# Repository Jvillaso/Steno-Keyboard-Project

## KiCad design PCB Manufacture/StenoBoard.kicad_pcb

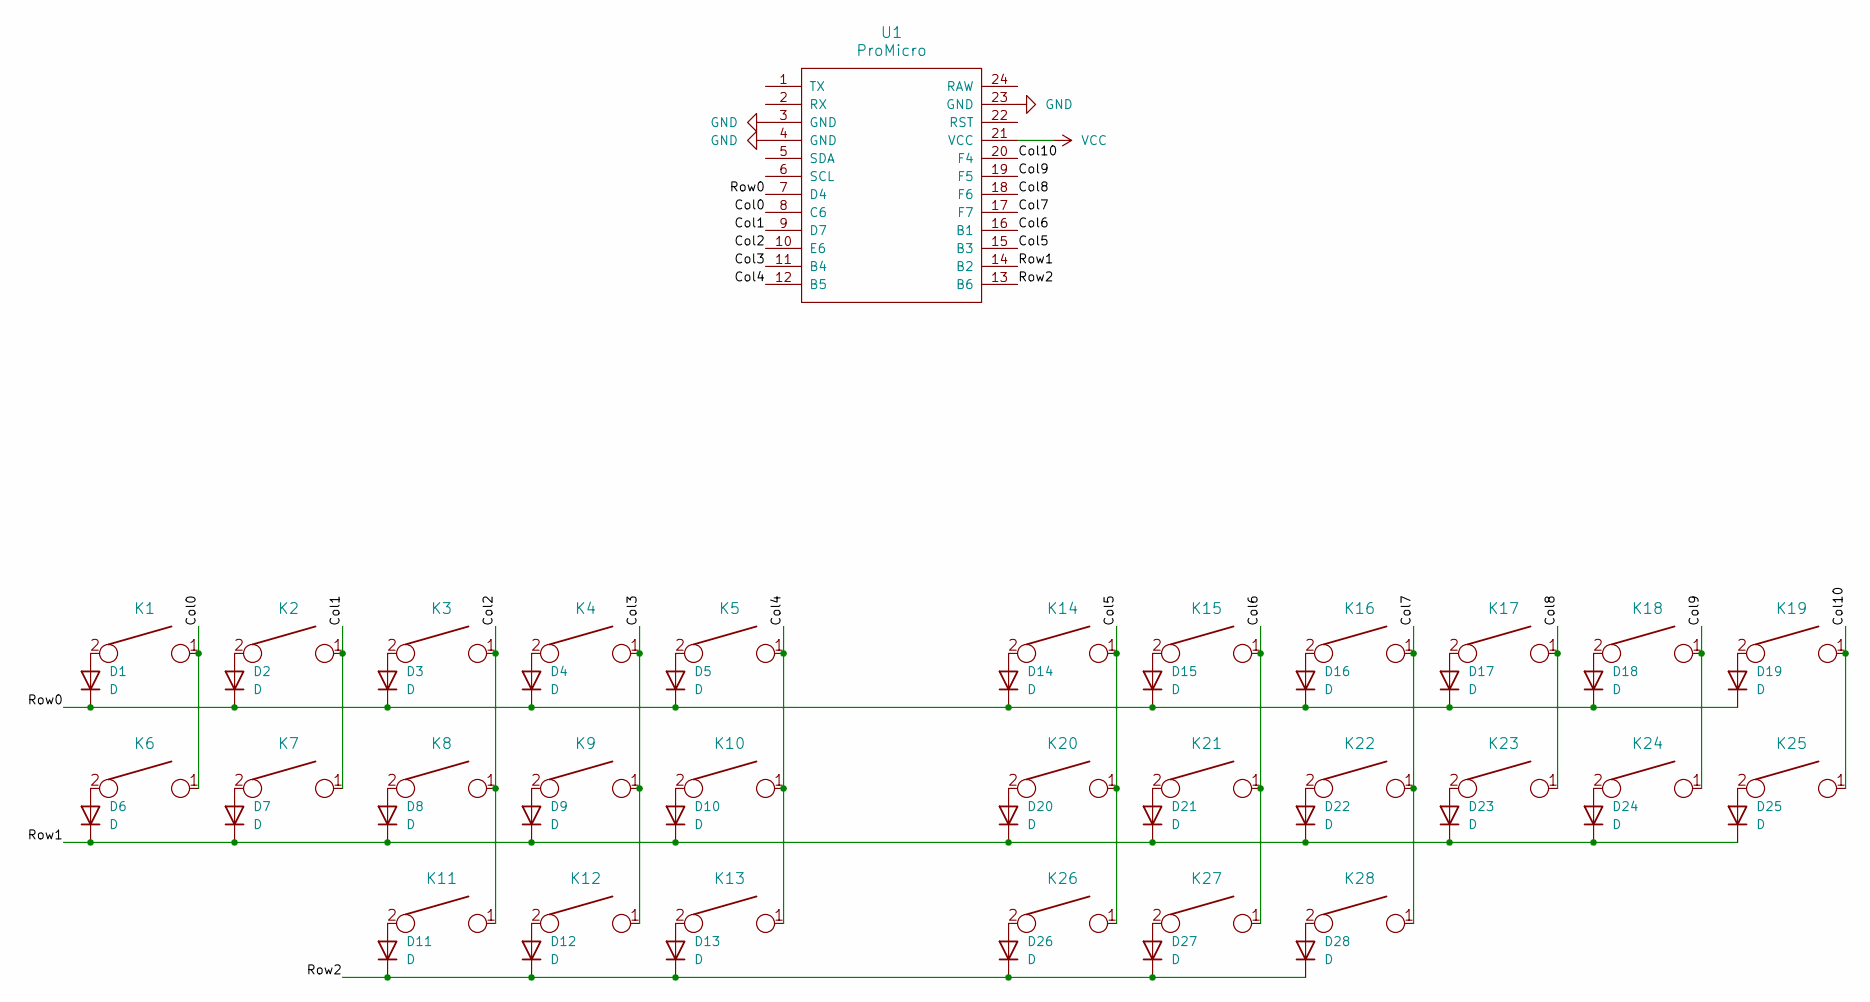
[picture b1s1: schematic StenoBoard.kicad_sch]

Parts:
D1, D2, D3, D4, D5, D6, D7, D8, D9, D10, D11, D12, D13, D14, D15, D16, D17, D18, D19, D20, D21, D22, D23, D24, D25, D26, D27, D28: D; D_SOD123
K1, K2, K3, K4, K5, K6, K7, K8, K9, K10, K11, K12, K13, K14, K15, K16, K17, K18, K19, K20, K21, K22, K23, K24, K25, K26, K27, K28: KEYSW; Mx_Alps_125
U1: ProMicro; ProMicro-EnforcedTop

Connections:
/Col0: K1.1, K6.1, U1.8 (C6)
/Col1: K2.1, K7.1, U1.9 (D7)
/Col2: K3.1, K8.1, K11.1, U1.10 (E6)
/Col3: K4.1, K9.1, K12.1, U1.11 (B4)
/Col4: K5.1, K10.1, K13.1, U1.12 (B5)
/Col5: K14.1, K20.1, K26.1, U1.15 (B3)
/Col6: K15.1, K21.1, K27.1, U1.16 (B1)
/Col7: K16.1, K22.1, K28.1, U1.17 (F7)
/Col8: K17.1, K23.1, U1.18 (F6)
/Col9: K18.1, K24.1, U1.19 (F5)
/Col10: K19.1, K25.1, U1.20 (F4)
/Row0: D1.1 (K), D2.1 (K), D3.1 (K), D4.1 (K), D5.1 (K), D14.1 (K), D15.1 (K), D16.1 (K), D17.1 (K), D18.1 (K), D19.1 (K), U1.7 (D4)
/Row1: D6.1 (K), D7.1 (K), D8.1 (K), D9.1 (K), D10.1 (K), D20.1 (K), D21.1 (K), D22.1 (K), D23.1 (K), D24.1 (K), D25.1 (K), U1.14 (B2)
/Row2: D11.1 (K), D12.1 (K), D13.1 (K), D26.1 (K), D27.1 (K), D28.1 (K), U1.13 (B6)
GND: U1.3 (GND), U1.4 (GND), U1.23 (GND)
unnamed: D1.2 (A), K1.2
unnamed: D2.2 (A), K2.2
unnamed: D3.2 (A), K3.2
unnamed: D4.2 (A), K4.2
unnamed: D5.2 (A), K5.2
unnamed: D6.2 (A), K6.2
unnamed: D7.2 (A), K7.2
unnamed: D8.2 (A), K8.2
unnamed: D9.2 (A), K9.2
unnamed: D10.2 (A), K10.2
unnamed: D11.2 (A), K11.2
unnamed: D12.2 (A), K12.2
unnamed: D13.2 (A), K13.2
unnamed: D14.2 (A), K14.2
unnamed: D15.2 (A), K15.2
unnamed: D16.2 (A), K16.2
unnamed: D17.2 (A), K17.2
unnamed: D18.2 (A), K18.2
unnamed: D19.2 (A), K19.2
unnamed: D20.2 (A), K20.2
unnamed: D21.2 (A), K21.2
unnamed: D22.2 (A), K22.2
unnamed: D23.2 (A), K23.2
unnamed: D24.2 (A), K24.2
unnamed: D25.2 (A), K25.2
unnamed: D26.2 (A), K26.2
unnamed: D27.2 (A), K27.2
unnamed: D28.2 (A), K28.2
VCC: U1.21 (VCC)

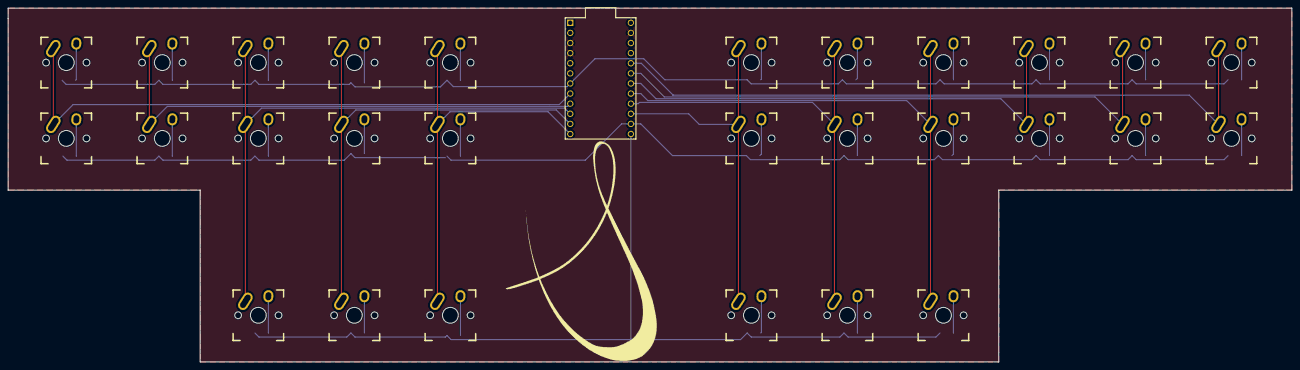
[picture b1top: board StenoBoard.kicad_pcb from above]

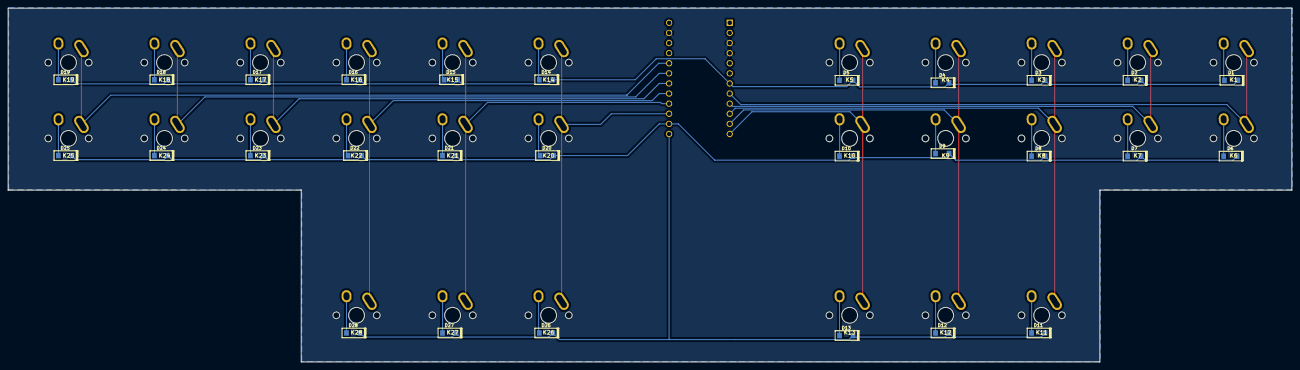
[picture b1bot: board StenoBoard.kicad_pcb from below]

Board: 2 copper layers, 322.6 x 88.9 mm, 57 parts (28 on the bottom side), 43 nets.

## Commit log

2024-06-12 QMK Implementation Updated
